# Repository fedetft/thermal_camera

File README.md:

Thermal camera
===============

An open source thermal camera, including firmware, schematic and PCB design.

How to build
============

This guide assumes you already have a Miosix build environment installed, if not see
[here](https://miosix.org/wiki/index.php?title=Linux_Quick_Start).

```
# Dependencies (should work both on Linux and WSL)
sudo apt install build-essential cmake libboost-all-dev libpng-dev

# Submodules
git submodule init
git submodule update

# Build mxgui code generators for embedding images and fonts
cd mxgui/_tools/code_generators
chmod +x compile_freetype.sh
mkdir build
cd build
cmake ..
make

# Build the thermal camera application
cd ../../../..
make -j`nproc`
```

How to flash
============

Install the dfu-util program on your pc.

Connect the USB cable between the PC an thermal camera, while the camera is off.

Use a jumper wire to connect BOOT0 (on the 4 pin header) to +3.3V (a convenient
spot is a capacitor next to the voltage regulator). You can just hold the wire
with your hands.

While the jumper is in place, press and hold the power on button of the camera.

You can disconnect the jumper but keep holding the power button. If you release
the power button, you need to reconnect the jumper and start again.

On the PC, run the command while holding the power button.
```
dfu-util -a 0 -s 0x08000000:leave -D main.bin
```

You should see a progress bar on the PC, keep holding the power button till the
progress bar reaches 100%.

Release the power button, and disconnect the USB cable.

Power on the camera and enjoy the new firmware. You cannot brick the camera,
if something goes wrong you can repeat the operation.

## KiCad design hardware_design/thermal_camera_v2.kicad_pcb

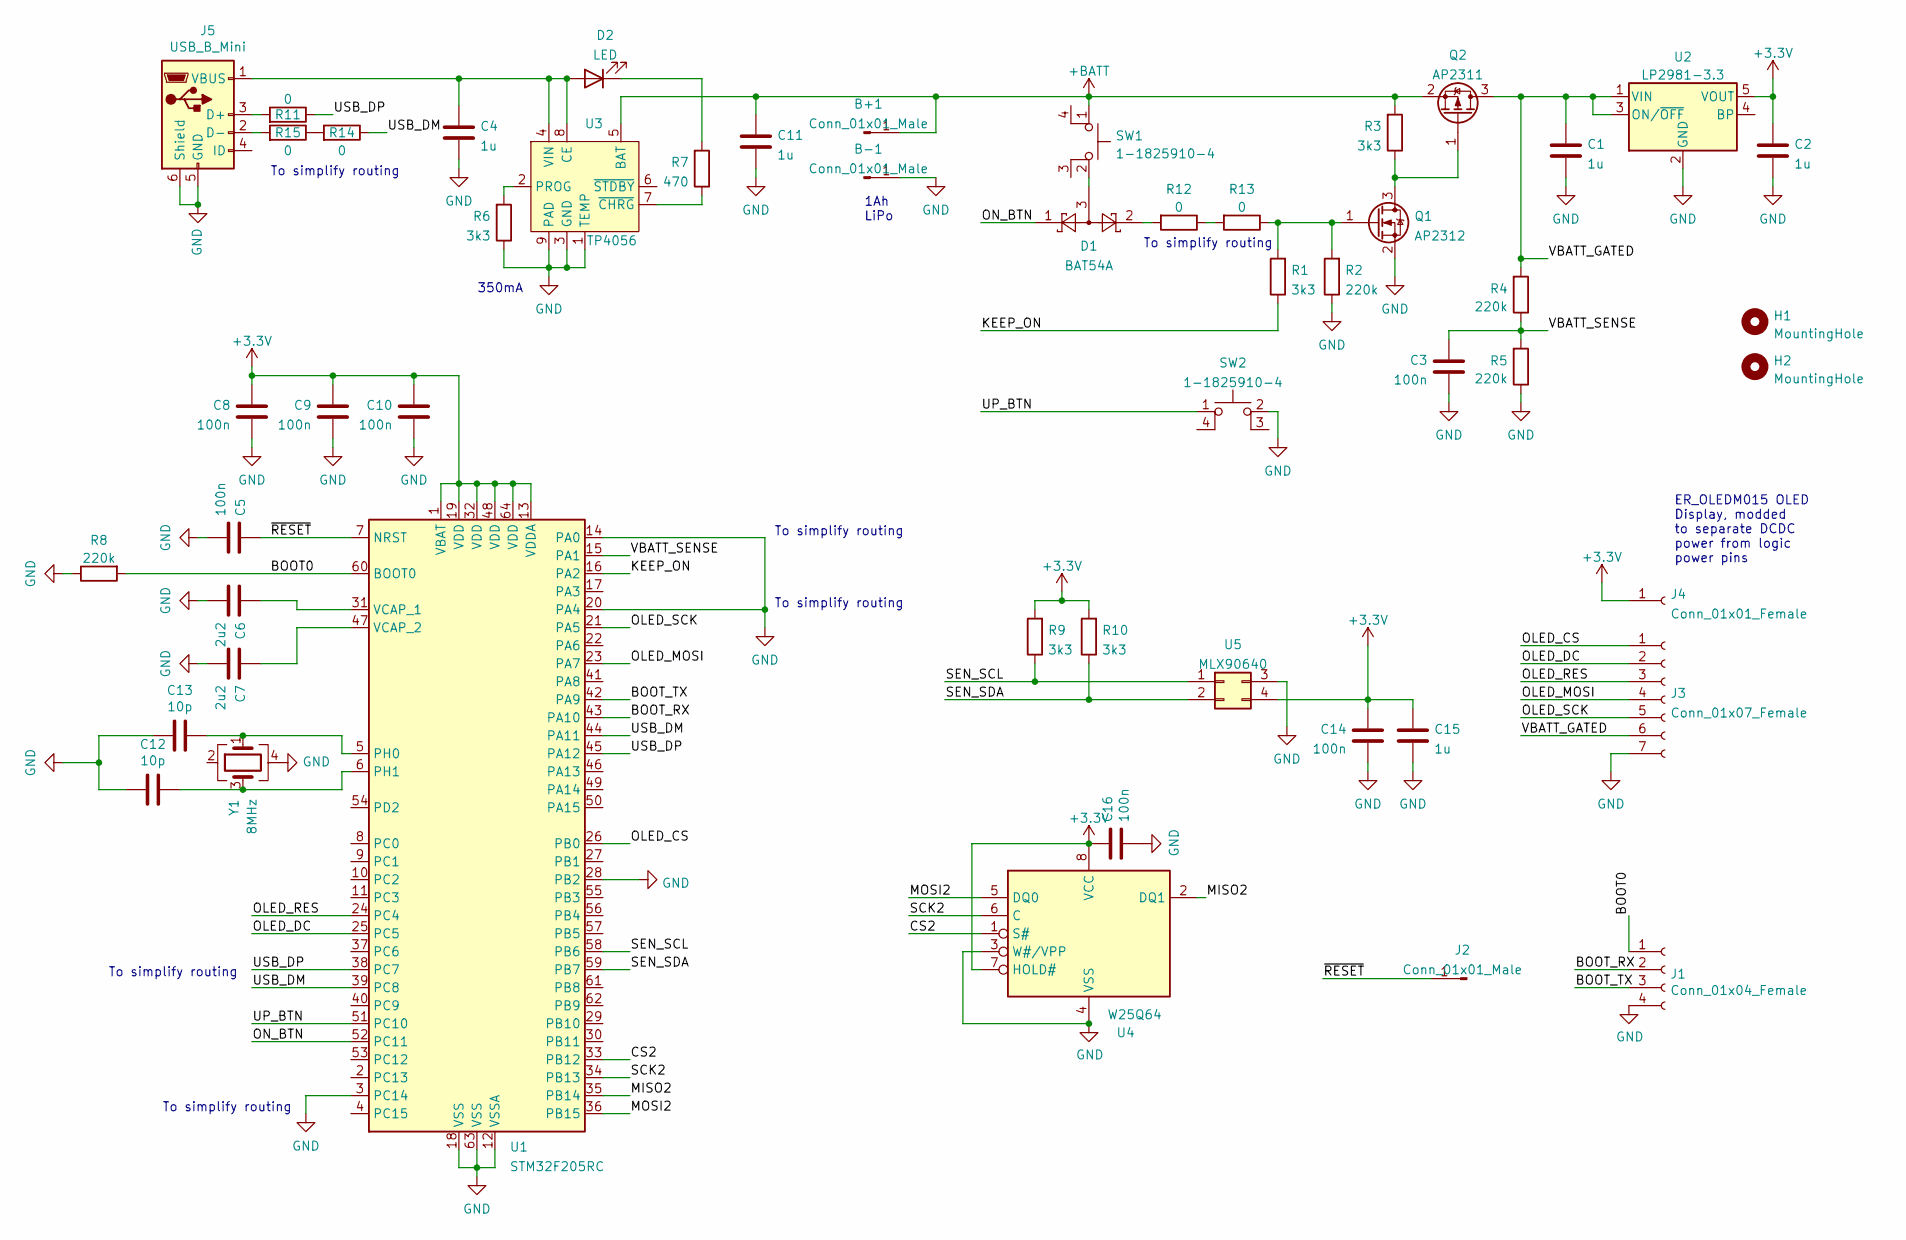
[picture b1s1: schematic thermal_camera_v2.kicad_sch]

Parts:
B+1: Conn_01x01_Male; PinHeader_1x01_P2.54mm_Vertical
B-1: Conn_01x01_Male; PinHeader_1x01_P2.54mm_Vertical
C1, C2, C4, C11, C15: 1u; C_0805_2012Metric_Pad1.18x1.45mm_HandSolder
C3, C5, C8, C9, C10, C14: 100n; C_0603_1608Metric_Pad1.08x0.95mm_HandSolder
C6, C7: 2u2; C_0805_2012Metric_Pad1.18x1.45mm_HandSolder
C12, C13: 10p; C_0603_1608Metric
C16: 100n; C_0603_1608Metric
D1: BAT54A; SOT-23
D2: LED; LED_0603_1608Metric_Pad1.05x0.95mm_HandSolder
H1, H2: MountingHole; MountingHole_2.1mm
J1: Conn_01x04_Female; PinSocket_1x04_P2.54mm_Vertical
J2: Conn_01x01_Male; PinHeader_1x01_P2.54mm_Vertical
J3: Conn_01x07_Female; PinSocket_1x07_P2.54mm_Vertical
J4: Conn_01x01_Female; PinSocket_1x01_P2.54mm_Vertical
J5: USB_B_Mini; USB_mini_china_unknown
Q1: AP2312; SOT-23
Q2: AP2311; SOT-23
R1, R3, R6, R9, R10: 3k3; R_0603_1608Metric_Pad0.98x0.95mm_HandSolder
R2, R4, R5, R8: 220k; R_0603_1608Metric_Pad0.98x0.95mm_HandSolder
R7: 470; R_0603_1608Metric_Pad0.98x0.95mm_HandSolder
R11, R12, R13, R14, R15: 0; R_0603_1608Metric_Pad0.98x0.95mm_HandSolder
SW1, SW2: 1-1825910-4; SW_PUSH_6mm
U1: STM32F205RC; LQFP-64_10x10mm_P0.5mm
U2: LP2981-3.3; SOT-23-5
U3: TP4056; SOIC-8-1EP_3.9x4.9mm_P1.27mm_EP2.29x3mm
U4: W25Q64; SOIC-8W_5.3x5.3mm_P1.27mm
U5: MLX90640; PinSocket_2x02_P2.54mm_Vertical
Y1: 8MHz; Crystal_SMD_5032-4Pin_5.0x3.2mm

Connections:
+3V3: C2.1, C8.2, C9.2, C10.2, C14.2, C15.1, C16.1, J4.1, R9.2, R10.2, U1.1 (VBAT), U1.13 (VDDA), U1.19 (VDD), U1.32 (VDD), U1.48 (VDD), U1.64 (VDD), U2.5 (VOUT), U4.7 (HOLD#), U4.8 (VCC), U5.4
+BATT: B+1.1, C11.1, Q2.2 (S), R3.2, SW1.1, U3.5 (BAT)
/BOOT0: J1.1, R8.2, U1.60 (BOOT0)
/BOOT_RX: J1.2, U1.43 (PA10)
/BOOT_TX: J1.3, U1.42 (PA9)
/CS2: U1.33 (PB12), U4.1 (S#)
/KEEP_ON: R1.1, U1.16 (PA2)
/MISO2: U1.35 (PB14), U4.2 (DQ1)
/MOSI2: U1.36 (PB15), U4.5 (DQ0)
/OLED_CS: J3.1, U1.26 (PB0)
/OLED_DC: J3.2, U1.25 (PC5)
/OLED_MOSI: J3.4, U1.23 (PA7)
/OLED_RES: J3.3, U1.24 (PC4)
/OLED_SCK: J3.5, U1.21 (PA5)
/ON_BTN: D1.1, U1.52 (PC11)
/SCK2: U1.34 (PB13), U4.6 (C)
/SEN_SCL: R9.1, U1.58 (PB6), U5.1
/SEN_SDA: R10.1, U1.59 (PB7), U5.2
/UP_BTN: SW2.1, U1.51 (PC10)
/USB_DM: R14.1, U1.39 (PC8), U1.44 (PA11)
/USB_DP: R11.1, U1.38 (PC7), U1.45 (PA12)
/VBATT_GATED: C1.1, J3.6, Q2.3 (D), R4.2, U2.1 (VIN), U2.3 (ON/~OFF)
/VBATT_SENSE: C3.2, R4.1, R5.2, U1.15 (PA1)
/~RESET: C5.2, J2.1, U1.7 (NRST)
GND: B-1.1, C1.2, C2.2, C3.1, C4.2, C5.1, C6.2, C7.2, C8.1, C9.1, C10.1, C11.2, C12.2, C13.2, C14.1, C15.2, C16.2, J1.4, J3.7, J5.5 (GND), J5.6 (Shield), Q1.2 (S), R2.1, R5.1, R6.1, R8.1, SW2.2, U1.3 (PC14), U1.12 (VSSA), U1.14 (PA0), U1.18 (VSS), U1.20 (PA4), U1.28 (PB2), U1.63 (VSS), U2.2 (GND), U3.1 (TEMP), U3.3 (GND), U3.9 (PAD), U4.3 (W#/VPP), U4.4 (VSS), U5.3, Y1.4
unnamed: C4.1, D2.2 (A), J5.1 (VBUS), U3.4 (VIN), U3.8 (CE)
unnamed: C6.1, U1.31 (VCAP_1)
unnamed: C7.1, U1.47 (VCAP_2)
unnamed: C12.1, U1.6 (PH1), Y1.3
unnamed: C13.1, U1.5 (PH0), Y1.1
unnamed: D1.2, R12.2
unnamed: D1.3, SW1.2
unnamed: D2.1 (K), R7.2
unnamed: J5.2 (D-), R15.2
unnamed: J5.3 (D+), R11.2
unnamed: Q1.1 (G), R1.2, R2.2, R13.1
unnamed: Q1.3 (D), Q2.1 (G), R3.1
unnamed: R6.2, U3.2 (PROG)
unnamed: R7.1, U3.7 (~CHRG)
unnamed: R12.1, R13.2
unnamed: R14.2, R15.1

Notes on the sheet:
To simplify routing
ER_OLEDM015 OLED Display, modded to separate DCDC power from logic power pins
350mA
1Ah LiPo

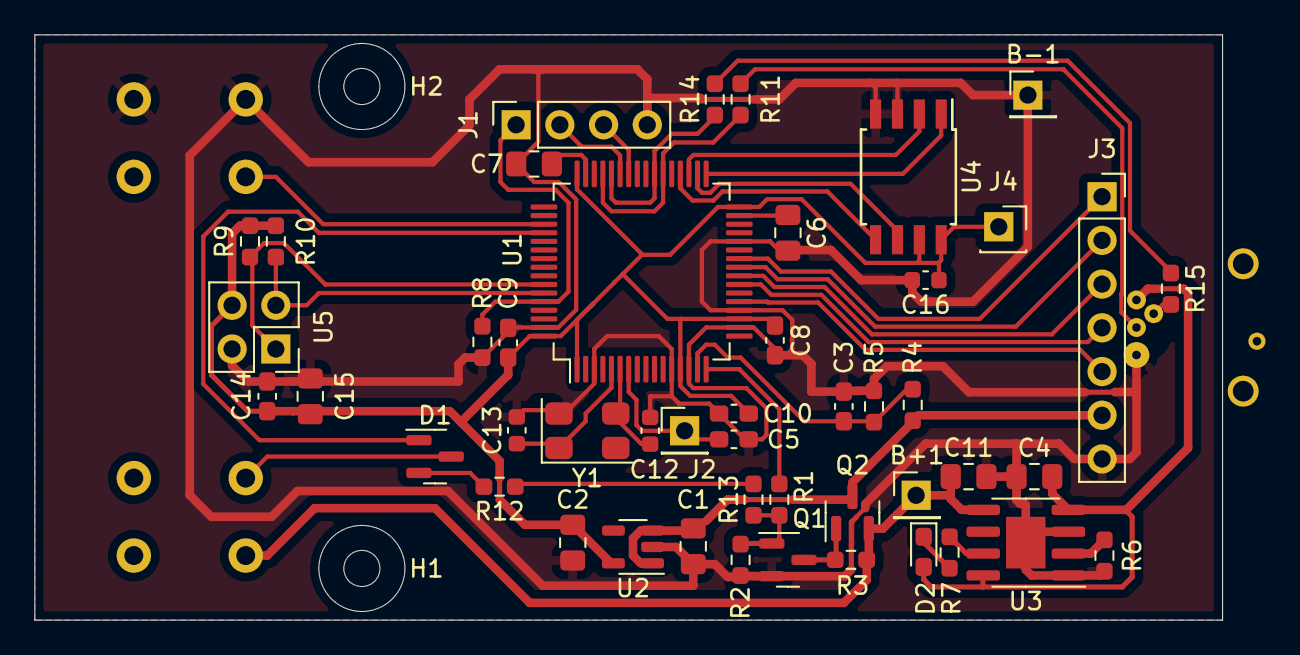
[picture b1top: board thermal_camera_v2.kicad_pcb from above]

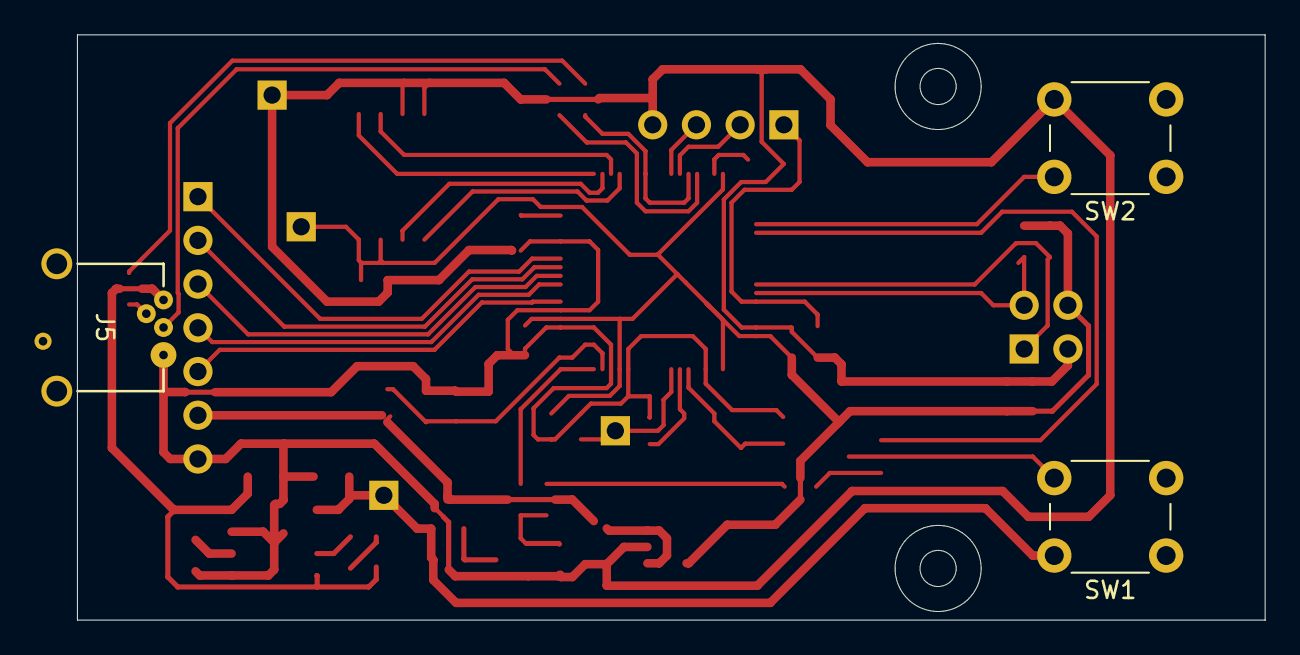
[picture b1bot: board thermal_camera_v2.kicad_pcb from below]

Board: 2 copper layers, 69.0 x 34.0 mm, 52 parts (3 on the bottom side), 41 nets.

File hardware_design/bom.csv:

Qty,Reference(s),Value,Footprint
5,"R1, R3, R6, R9, R10",3k3,Resistor_SMD:R_0603_1608Metric
4,"R2, R4, R5, R8",220k,Resistor_SMD:R_0603_1608Metric
1,R7,470,Resistor_SMD:R_0603_1608Metric
5,"R11, R12, R13, R14, R15",0,Resistor_SMD:R_0603_1608Metric
5,"C1, C2, C4, C11, C15",1u,Capacitor_SMD:C_0805_2012Metric
7,"C3, C5, C8, C9, C10, C14, C16",100n,Capacitor_SMD:C_0603_1608Metric
2,"C6, C7",2u2,Capacitor_SMD:C_0805_2012Metric
2,"C12, C13",10p,Capacitor_SMD:C_0603_1608Metric
1,D1,BAT54A,SOT-23
1,D2,LED,LED_SMD:LED_0603_1608Metric
1,J1,4 pin serial/programming connector,Connector_PinSocket_2.54mm
0,J2,Do not fit,
1,"J3, J4",ER_OLEDM015 OLED color 128x128,"https://www.ebay.com/itm/401236987473 NOTE: requires modding to separate DCDC power from logic power, soldering an unmodded display will damage it!"
1,J5,USB_B_Mini,TE Connectivity:2172034-1
1,Q1,AP2312 / SI2312,SOT-23
1,Q2,AP2311 / SI2311,SOT-23
2,"SW1, SW2",1-1825910-4,SW_PUSH_6mm TE connectivity:1-1825910-4 Mouser:506-1-1825910-4
1,U1,STM32F205RC,LQFP-64
1,U2,LP2981-3.3,SOT-23-5
1,U3,TP4056,SOIC-8-1EP
1,U4,W25Q64,SOIC-8W
1,U5,MLX90640,NOTE: Requires bending pins for right angle mount
1,Y1,8MHz,ABRACON ABM3B-8.000MHZ-10-1-U-T
1,"B+1, B-1",LiPo battery 1Ah,https://www.ebay.com/itm/123867825568

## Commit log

2022-02-26 Added miosix-kernel as a git submodule
2022-02-26 Added mxgui as a git submodule
2022-02-26 First test code
2022-02-27 First working version
2022-03-07 Comments
2022-03-13 Fix rotation
2022-03-21 Const is your friend
2022-03-21 After a long time, first hardware I2C working, still needs cleanup
2022-03-21 Beginning cleanup
2022-03-27 Adapting to updated I2C driver
2022-03-27 Use new sendRecv of I2C driver and simplify code
2022-03-27 Gitignore
2022-03-27 Updated kernel, updated config
2022-04-03 Improved MLX90640 algorithms to never use double (30% speed improvement), added thread-able mlx90640 driver to read sensor code, refacored application to use threads, max speed for now 4Hz
2022-04-03 Optimized display draw to a single image draw call, that made 8fps possible also without DMA
2022-04-05 First version of DMA-accelerated display image drawing
2022-04-05 Added images directory with icons
2022-04-05 Logo and battery icon
2022-04-06 New colormap and icons
2022-04-06 Refactored application to make room for more complex application code
2022-04-06 Added colormap encoder
2022-04-06 Removed temporary file
2022-04-09 Main frame of the UI completed
2022-04-09 optimized scanLine with DMA, faster serial port
2022-04-09 Short mode, made rendering 6x faster but at a loss of image quality
2022-04-10 Getting back some of the image depth by scaling
2022-04-10 Now with more comments! And better error code paths too!
2022-11-01 Begin menu UI
2022-11-03 Menu working except save option
2022-11-04 Decoupled UI loop from sensor refresh to prevent slow UI at slow fps
2022-11-06 Added options saving to flash
2022-11-06 Added Kicad pcb files
2022-11-07 Updated submodule
2022-11-07 Added readme
2022-11-18 Fix button part number, add components BOM
2022-11-18 Switched XTAL footprint
2022-11-19 Specified full sensor part number
2022-12-18 Documented display mod
2022-12-26 mlx90640 driver: Sleep for 80ms before attempting to read the EEPROM.
2022-12-26 Update gitignore to include KiCad temporary files.
2022-12-26 Update mxgui.
2023-02-08 Added interactive bill of material
2023-02-21 Ignore all CMake build directories.
2023-02-21 Improve menu UI flow.
2023-02-21 Use Miosix threads instead of std::thread.
    The main motivation is to get rid of the redundancy between the sensorThreadId attribute and the st local inside Application::run().
    We were already using Miosix-specific priority features so this also ends up cleaning the code further.
2023-02-21 Add autorepeat to the menu.
2023-02-21 Modify ApplicationUI to use a state-machine-like pattern.
2023-02-21 Turn off board only with a long press of the on button.
2023-02-21 Make ApplicationUI conform to the coding style of the rest of the project.
2023-02-21 Fix button state initializer.
2023-02-21 Fix a bug where shutdown would deadlock if acquisition is paused.
2023-02-21 Update the battery icon from ApplicationUI.
2023-02-21 Fix an off-by-one error in the textbox paint code.
2023-02-21 Add a (UI only) simulator.
2023-02-21 Add a feature for pausing acquisition by pressing the ON/OFF button.
2023-02-21 Also print the version number from git together with the Miosix version in the secret screen.
2023-02-21 Split hardware-dependent logic from UI logic.
2023-02-21 Reduce overpaint when drawing the menu.
2023-02-21 Re-paint the thermal image at each application mode transition.
2023-02-21 Add a secret feature for displaying the Miosix version when the up button is pressed at boot.
2023-02-21 Add a class for drawing multiple lines of text.
2023-02-21 Do not use private symbols starting with 2 underscores.
2023-02-21 Move the colormap encoder into _tools.
2023-03-14 Update miosix submodule.
2023-03-14 Use CPUTimeCounter for profiling.
2023-03-14 Optimize the sensor processing code by using fast inverse square root and better compilation options.
2023-03-14 Fix inconsistent whitespace in the MLX90640 code.
2023-03-14 16 fps mode
2023-03-16 Properly put the current thread to sleep when waiting for SPI DMA rather than polling almost all the time.
2023-03-16 Optimize the image interpolation code.
    Not the most useful optimization.
2023-04-04 Update miosix submodule again.
2023-04-27 ApplicationUI: Optimize handling of the drawing context.
2023-04-27 Update Miosix submodule reference
2023-05-27 Add a missing call to setTextColor.
2023-05-27 Make the pointer to thermal_camera_version a true compile time constant.
2023-05-27 Integrate tinyusb into the build system.
2023-05-27 Add tinyusb submodule.
2023-05-27 Update miosix again.
2023-10-15 Add USB CDC driver class implemented as a frontend for tinyUSB.
2023-10-15 Add USB connection indicator to the UI.
2023-10-15 Add function for retrieving MLX90640 EEPROM contents even after device initialization.
2023-10-15 Add USB communication threads and the ability to stream frames in real time.
2023-10-15 Do not lock up when reads to the I2C bus repeatedly fail.
2023-10-15 Remove unused original Melexis I2C code.
2023-10-15 Move frame processing code out of the MLX90640 driver.
2023-10-15 Simulator: add support for getting frames from other sources
2023-10-15 Add the ability to stream images from a physical device in the simulator.
2023-10-15 Make it work for Linux as well.
2023-11-05 Add brightness option
2023-11-06 Fix a deadlock issue that could manifest when exiting the menu.
    The lastFrameMutex was held when drawing a frame, which could cause a deadlock when the render thread attempts to draw a frame while the main thread is already drawing the UI. The render thread canno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
    The fix changes lastFrameMutex to only protect the actual modifications to lastFrame.
2024-04-20 Added flashing guide through USB
2026-05-03 Updated kernel to v3.01
2026-05-03 Updated config and Makefiles to Miosix 3
2026-05-03 The textbox is now part of mxgui
2026-05-03 Update application and drivers to Miosix 3
2026-05-09 Update build instructions for Miosix 3
2026-05-09 Add pictures
